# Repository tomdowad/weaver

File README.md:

# weaver
A collection of circuit boards and methods in support of reusable modular electronics

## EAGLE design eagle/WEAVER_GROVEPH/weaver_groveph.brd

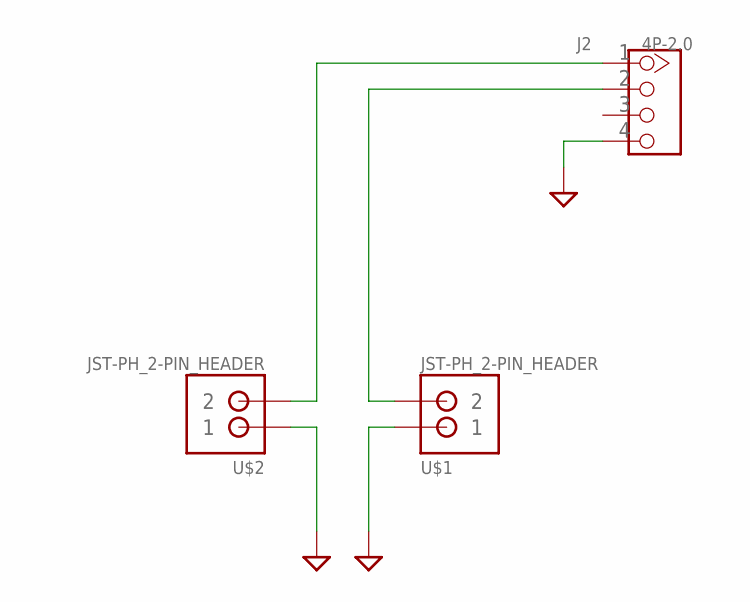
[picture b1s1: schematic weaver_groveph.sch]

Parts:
J2: 4P-2.0; HW4-2.0
U$1, U$2: JST-PH_2-PIN_HEADER; JST_B2B-PH_HEADER

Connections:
GND: J2.4, U$1.P1 (1), U$2.P1 (1)
unnamed: J2.1, U$2.P2 (2)
unnamed: J2.2, U$1.P2 (2)

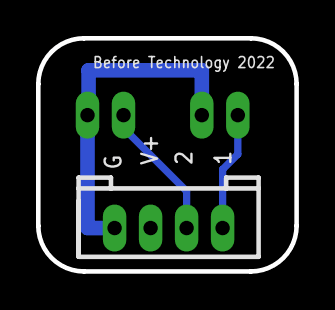
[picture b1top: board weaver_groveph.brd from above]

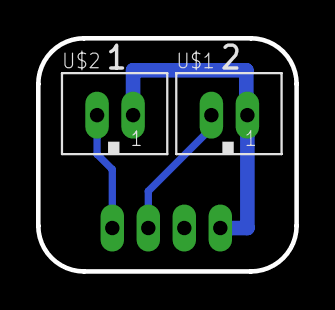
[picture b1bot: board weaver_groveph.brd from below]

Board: 2 copper layers, 14.4 x 13.0 mm, 3 parts (2 on the bottom side), 3 nets.

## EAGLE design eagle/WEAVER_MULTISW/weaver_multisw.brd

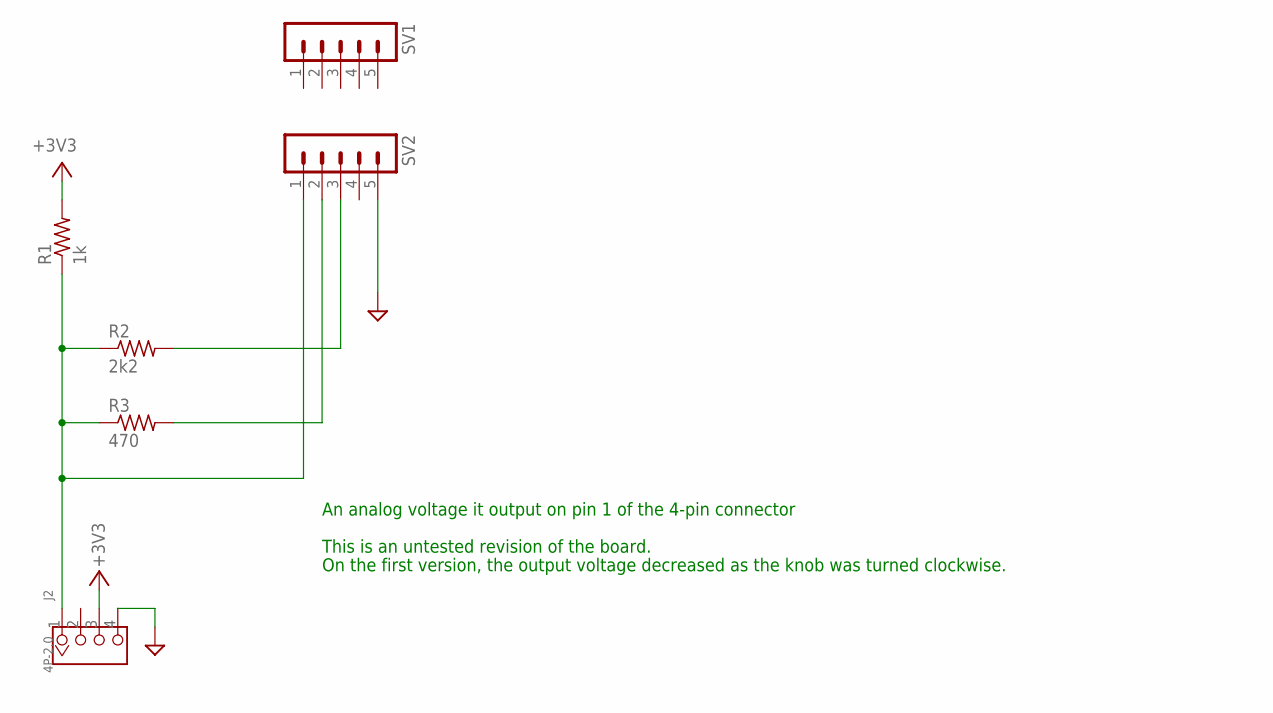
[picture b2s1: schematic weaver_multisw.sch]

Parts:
J2: 4P-2.0; HW4-2.0
R1: 1k; R0805
R2: 2k2; R0805
R3: 470; R0805
SV1, SV2: MA05-1

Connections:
GND: J2.4, SV2.5
unnamed: J2.1, R1.1, R2.1, R3.1, SV2.1
unnamed: R2.2, SV2.3
unnamed: R3.2, SV2.2
V+: J2.3, R1.2

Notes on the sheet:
An analog voltage it output on pin 1 of the 4-pin connector
This is an untested revision of the board.
On the first version, the output voltage decreased as the knob was turned clockwise.

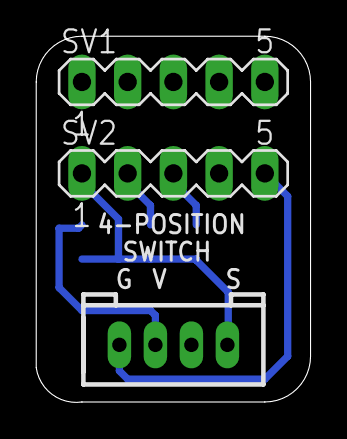
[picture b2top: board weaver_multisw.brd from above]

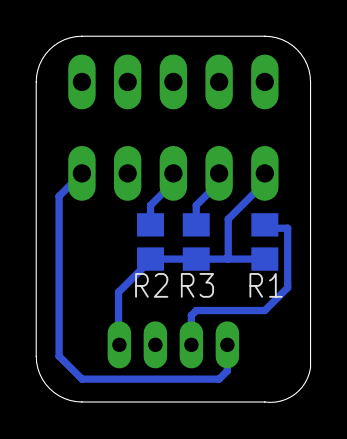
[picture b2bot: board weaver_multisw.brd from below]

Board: 2 copper layers, 15.2 x 20.3 mm, 6 parts (3 on the bottom side), 5 nets.

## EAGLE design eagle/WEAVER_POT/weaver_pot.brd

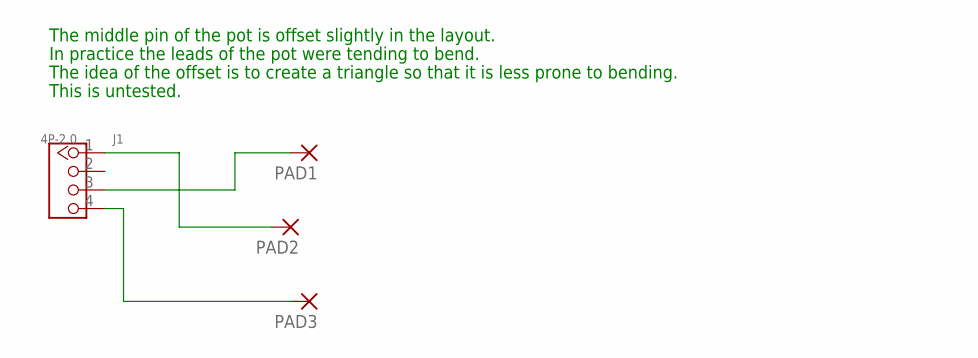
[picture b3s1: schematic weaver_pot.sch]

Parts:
J1: 4P-2.0; HW4-2.0
PAD1, PAD2, PAD3: 3,81/1,1

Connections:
unnamed: J1.4, PAD3.1
unnamed: J1.3, PAD1.1
unnamed: J1.1, PAD2.1

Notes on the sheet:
The middle pin of the pot is offset slightly in the layout.
In practice the leads of the pot were tending to bend.
The idea of the offset is to create a triangle so that it is less prone to bending.
This is untested.

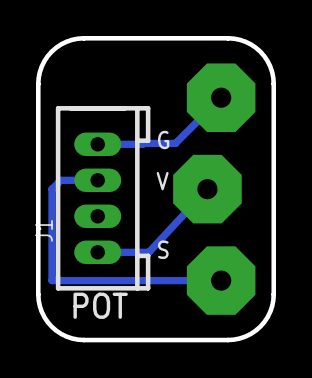
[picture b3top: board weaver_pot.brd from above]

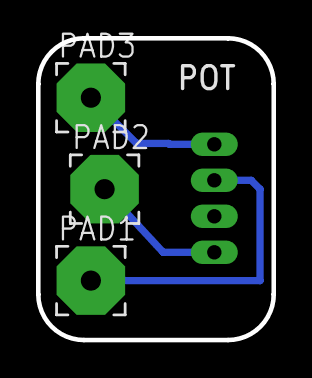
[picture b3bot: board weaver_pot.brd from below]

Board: 2 copper layers, 13.1 x 16.8 mm, 4 parts (3 on the bottom side), 3 nets.

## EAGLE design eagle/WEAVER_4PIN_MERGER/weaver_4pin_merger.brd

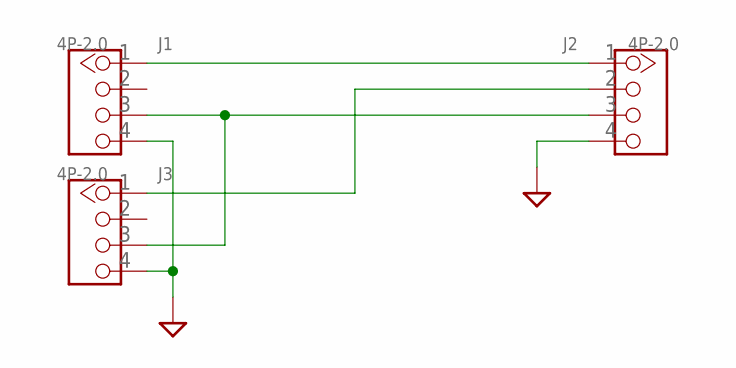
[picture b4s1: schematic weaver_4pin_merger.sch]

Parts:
J1, J2, J3: 4P-2.0; HW4-2.0

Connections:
GND: J1.4, J2.4, J3.4
unnamed: J1.1, J2.1
unnamed: J2.2, J3.1
unnamed: J1.3, J2.3, J3.3

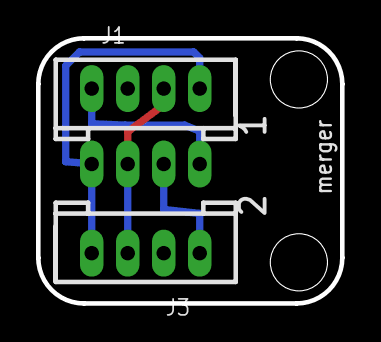
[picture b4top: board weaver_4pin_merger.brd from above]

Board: 2 copper layers, 16.9 x 14.7 mm, 3 parts (1 on the bottom side), 4 nets.

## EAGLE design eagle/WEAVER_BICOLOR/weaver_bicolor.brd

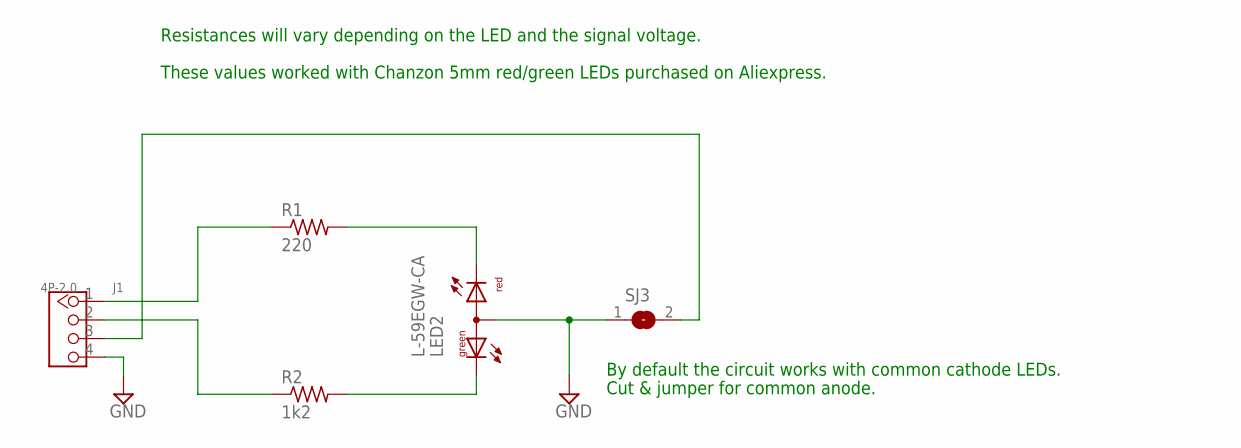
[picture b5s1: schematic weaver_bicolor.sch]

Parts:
J1: 4P-2.0; HW4-2.0
LED2: L-59EGW-CA
R1: 220; R0805
R2: 1k2; R0805
SJ3: SJ

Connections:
GND: J1.4, LED2.2 (A), SJ3.1
unnamed: LED2.1 (CR), R1.2
unnamed: LED2.3 (CG), R2.2
unnamed: J1.1, R1.1
unnamed: J1.2, R2.1
unnamed: J1.3, SJ3.2

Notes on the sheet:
By default the circuit works with common cathode LEDs.
Resistances will vary depending on the LED and the signal voltage.
These values worked with Chanzon 5mm red/green LEDs purchased on Aliexpress.
Cut & jumper for common anode.

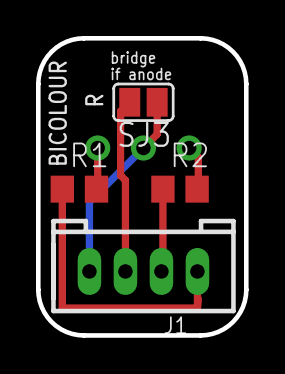
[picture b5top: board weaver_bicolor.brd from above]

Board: 2 copper layers, 11.6 x 16.5 mm, 5 parts (1 on the bottom side), 6 nets.

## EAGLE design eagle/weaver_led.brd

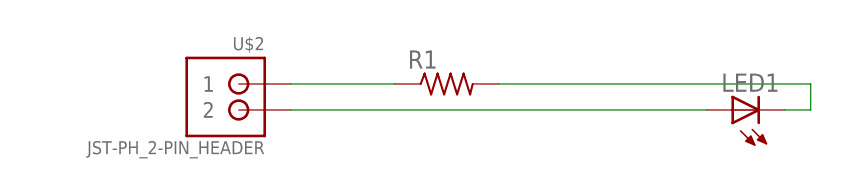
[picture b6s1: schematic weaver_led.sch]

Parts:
LED1: LED5MM
R1: R-US_R0805; R0805
U$2: JST-PH_2-PIN_HEADER; JST_B2B-PH_HEADER

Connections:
unnamed: LED1.K (C), R1.2
unnamed: R1.1, U$2.P1 (1)
unnamed: LED1.A, U$2.P2 (2)

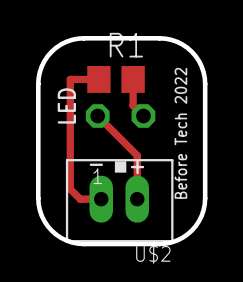
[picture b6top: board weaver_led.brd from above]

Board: 2 copper layers, 9.3 x 11.4 mm, 3 parts (1 on the bottom side), 3 nets.

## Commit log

2022-05-11 Create Eagle
